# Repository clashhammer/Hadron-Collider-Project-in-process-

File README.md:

# Hadron-Collider-Project-in-process-
A project that simulates how a particle moves in a hadron collider by spinning a metal ball inside a ring and is being pushed by electromagents.

This is one of my hardest projects so far, since it has been so prolongued and at the same time very resourse and time consuming. It is by now almost ready and soon me and my friend are going to finish it, but just so it doesn't stay untouched in my project library I will ship it and continue on later. :)

Anyways, since I saw the "physics lab" sidequest I decided to describe what me and my friend have calculated and how our project works and what it showcases.

PLAN OF THE PROJECT:
- The project revolves around hadron colliders. The idea is to showcase how they work, what they do and why do they do it. So a hadron collider is essentially a giant circle (the biggest right now is in CERN in Switzerland which is about 27km (~16.6 miles) in lenght, but in the USA there is a plan to make one that is about 100km (~62 miles) in lenght), that has a bunch of electromagnets. The point of these electromagnets is to push subatomic particles (protons, electrons and neutrons) to near lightspeed and collide them with eachother, hence why's it called a hadron collider. The idea of colliding these particles is to learn about fundamental particles, forces and events near the Big Bang that created the universe. Interesting fact is that the large hadron collider in CERN uses about 1.3 TERRAwatts of power annually which is enough to power 370,000 european households for a whole year (which is crazy to think about). 

THEORETICAL AND EXPERIMENTAL CONCLUSIONS OF OUR PROJECT:
- Thus far we have made a lot of calculations and our plan is flawless. We have concluded that a coil with less windings (about 150-180) is best for the induction (how fast electricity flows through the coil) and thus for the impulse power of the coil. The induction has to be very high so that the ball gets pushed with greater force and thus being faster. We have concluded with an experiment with a single coil and board that this is the best amount of windings. We have calculated the maximum speed + the timings of the coils. With the best timing and counting friction the maximum speed of the ball should be 7,3-7.4 m/s or about 24,3 ft/s. With slightly worse timing and counting friction we get about 4,8 m/s or about 15,8 ft/s. With the worst timing and counting friction we get 2 - 4 m/s or 6,6 - 13,1 ft/s. And you might ask what are these timings. Well the timings are the time between the coil powering on and the induction being at maximum. Since we use IR emmiter and receiver on the boards so that the coils aren't always activated so that they are not overheating, and have impulses of magnetic fields, we calculated that the time between the IR light being obstructed by the ball and the coil being at it's maximum induction and therefore the best timing is when the ir sensors are 1,5cm away from the CENTER of the coil. Finnaly we have calculated that each coil needs about 1,5A of current to operate propperly. That means that to finish this project I need to buy a charger that is at least 6A to support those 8 coils. More on that when we finish the project.

Here is a picture of the pcb schematic if you decide to make one of your own. There you can see all resistor values and stuff you need for the boards as well as where to place it. You can get the pcb files from the files and get it printed yourself by PCBWay or JLCPCB (That's what I use).

Shout out to my friend who made most of the calculations. He wants to be a theoretical physicist and knows a lot about how to calculate the stuff we needed to be calculated for this project. I was more on the practical and cirquitry side, gathering all the parts for the project, making a pcb design, making schematics and so on. 

Anyways, I'll redact this once the project is finally ready. Until then goodbye!

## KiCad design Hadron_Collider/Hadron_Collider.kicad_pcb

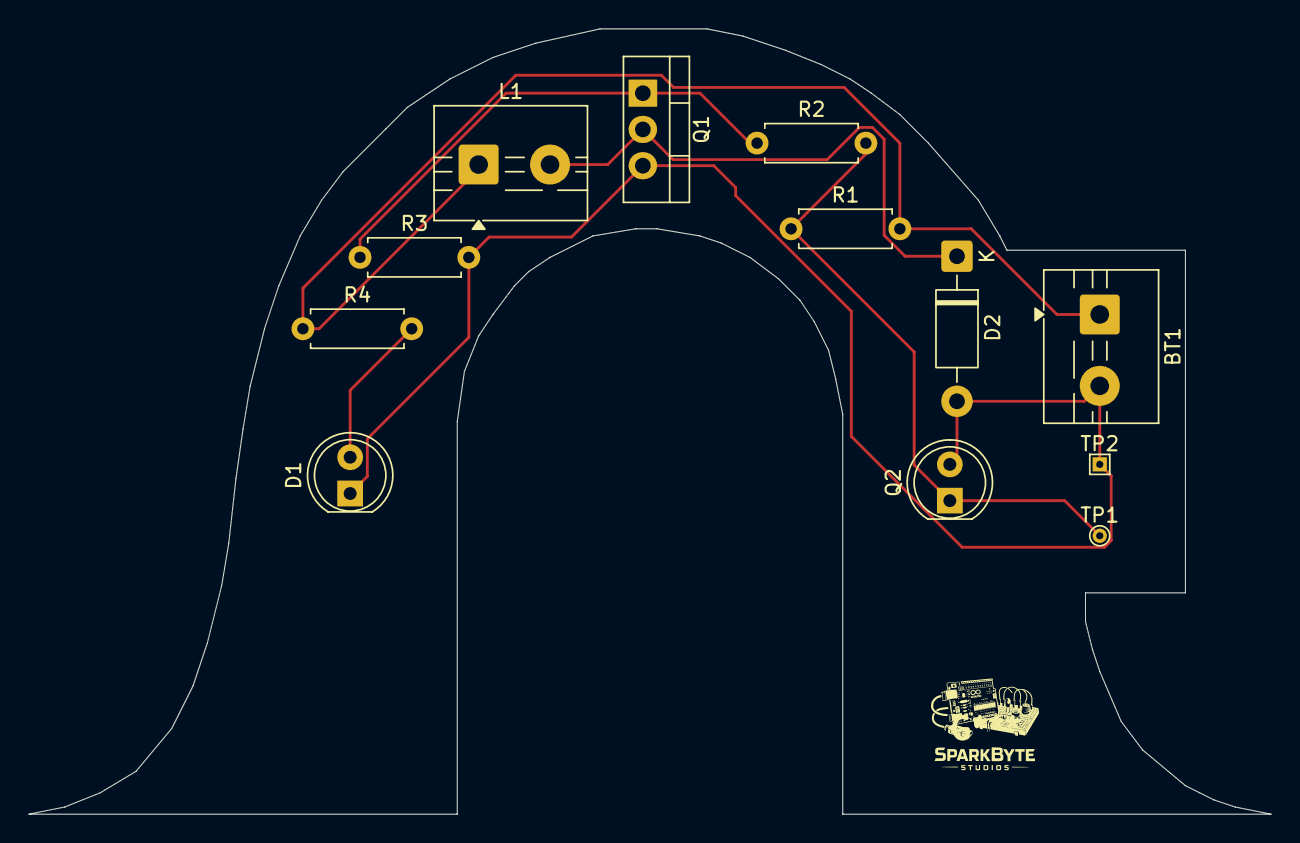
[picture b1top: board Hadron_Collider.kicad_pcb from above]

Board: 2 copper layers, 87.0 x 55.0 mm, 12 parts (0 on the bottom side), 6 nets.

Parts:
BT1: 12V, 2A; TerminalBlock_MaiXu_MX126-5.0-02P_1x02_P5.00mm
D1: LD271; LED_D5.0mm_Clear
D2: 1N4007; D_DO-41_SOD81_P10.16mm_Horizontal
L1: L; TerminalBlock_MaiXu_MX126-5.0-02P_1x02_P5.00mm
Q1: IRLZ44N; TO-220-3_Vertical
Q2: BPW40; LED_D5.0mm_Clear
R1, R3: 10KΩ; R_Axial_DIN0207_L6.3mm_D2.5mm_P7.62mm_Horizontal
R2: 47Ω; R_Axial_DIN0207_L6.3mm_D2.5mm_P7.62mm_Horizontal
R4: 220Ω; R_Axial_DIN0207_L6.3mm_D2.5mm_P7.62mm_Horizontal
TP1: TestPoint; TestPoint_THTPad_D1.0mm_Drill0.5mm
TP2: TestPoint; TestPoint_THTPad_1.0x1.0mm_Drill0.5mm

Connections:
unnamed: BT1.1 (+), L1.1, R1.2, R4.1
unnamed: BT1.2 (-), D1.1 (K), D2.2 (A), Q1.3 (S), Q2.2 (E), R3.2, TP2.1
unnamed: D1.2 (A), R4.2
unnamed: D2.1 (K), L1.2, Q1.2 (D)
unnamed: Q1.1 (G), R2.1, R3.1
unnamed: Q2.1 (C), R1.1, R2.2, TP1.1

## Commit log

2026-04-11 Schematic and PCB design for the coil boards.
2026-04-11 Explanation, calculations, experiments.
    Expanded project description and added theoretical and experimental conclusions.
2026-04-21 Files (schematic, pcb and gerber)
